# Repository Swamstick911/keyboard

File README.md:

# Mechatron

## About

Mechatron is a 65% mechanical keyboard. It has some features listed below:
- An OLED Display [SSD1306]
- A Rotary Encoder [EC11]
- RGB Underglow
- Tactile Switches

---

## Firmware

The firmware will be KMK which will be written in micropython, as I am using a Raspberry Pi Pico, it makes this easier. Still working on the firmware of the keyboard, for updates check the JOURNAL.md file!

---

## Bill of Materials (BOM)

| Name                                                          | Quantity   | Cost   | Link                                                                                                                                                                                                                                                                                                                                                                                                                                                                                                                                                 |
|:--------------------------------------------------------------|:-----------|:-------|:-----------------------------------------------------------------------------------------------------------------------------------------------------------------------------------------------------------------------------------------------------------------------------------------------------------------------------------------------------------------------------------------------------------------------------------------------------------------------------------------------------------------------------------------------------|
| Gateron EF Grayish                                            | 80         | $18.19 | https://neomacro.in/products/gateron-ef-grayish                                                                                                                                                                                                                                                                                                                                                                                                                                                                                                      |
| Durock Smokey Screw-In Stabilizers V2 (4+1 w/ 6.25u spacebar) | 1          | $18.58 | https://stackskb.com/store/durock-smokey-screw-in-stabilizers-v2/                                                                                                                                                                                                                                                                                                                                                                                                                                                                                    |
| Cherry Profile PBT Keycaps                                    | 1          | $15.15 | https://stackskb.com/store/veekos-gradient-keycaps-cherry-profile-135-keys/                                                                                                                                                                                                                                                                                                                                                                                                                                                                          |
| Diode 1N4148 Through-Hole                                     | 100        | $1.17  | https://www.amazon.in/dp/B084ZP5BJ3?ref_=cm_sw_r_cp_ud_dp_YPW3WFYTE31QA18570D1&_encoding=UTF8&psc=1                                                                                                                                                                                                                                                                                                                                                                                                                                                  |
| WS2812B RGB LED                                               | 8          | $2.76  | https://www.adafruit.com/product/1655                                                                                                                                                                                                                                                                                                                                                                                                                                                                                                                |
| Header 1x4 (I2C OLED)                                         | 1          | $0.10  | https://www.digikey.in/en/products/detail/amphenol-fci/20021121-00010T4LF/10014539                                                                                                                                                                                                                                                                                                                                                                                                                                                                   |
| OLED                                                          | 1          | $1.92  | https://www.amazon.in/Robodo-Electronics-D1286464-Display-Arduino/dp/B07B92SFJV?crid=22PDBSONP7I84&dib=eyJ2IjoiMSJ9._fc6m2CiLg2C4zbCzTKu5yG8fXhyDDnEzcq-tkJ5ONFzDwy16N8zf2l60QPbqxWQhk4mFtEJ5IH2EA0xsyK-mwiNFWFD_w9vg1a7mg-NjWp_56AFy1OO9-iygwyQk9sB69dxvDaZvVmbT36XL2-eg49dpzfKXk0bx13VoBi1Hhb1vG3RQP0P7Z7VCThHe2NjnwkjVfkNtYHWYOWzaG1JvLpacVPaWzxN3Uhdzq5UvlM.GtWvXxquAYLzol9vmMcDAWZhkUVFSIQtM6K3fH87alc&dib_tag=se&keywords=0.91%2Binch%2Boled%2Bdisplay%2Bi2c&qid=1755270026&sprefix=0.91%2Binch%2Boled%2Bdisplay%2Bi2%2Caps%2C384&sr=8-11&th=1 |
| Rotary Encoder EC11 w/ Push                                   | 1          | $2.00  | https://www.adafruit.com/product/377                                                                                                                                                                                                                                                                                                                                                                                                                                                                                                                 |
| I2C Expander (PCF8574)                                        | 1          | $0.83  | https://www.digikey.in/en/products/detail/nxp-usa-inc/PCF8574T-3-518/735505                                                                                                                                                                                                                                                                                                                                                                                                                                                                          |
| M3 x 20mm Bolt                                                | 15         | $1.73  | https://www.amazon.in/dp/B0CX99K2RL?ref_=cm_sw_r_cp_ud_dp_WPFQM677EMXT3KKH904P&_encoding=UTF8                                                                                                                                                                                                                                                                                                                                                                                                                                                        |
| M3 Nuts                                                       | 8          | $1.16  | https://www.amazon.in/dp/B09J92WY5Q?ref_=cm_sw_r_cp_ud_dp_7TEKARN0PX76YMEZR3TW&_encoding=UTF8&psc=1                                                                                                                                                                                                                                                                                                                                                                                                                                                  |
| M3 x 5mm Heatset Insert                                       | 25         | $2.09  | https://www.amazon.in/dp/B0CX1BS7DJ?ref_=cm_sw_r_cp_ud_dp_13RMQGNJ1CXSNS92NXVW                                                                                                                                                                                                                                                                                                                                                                                                                                                                       |
| PCB - (Black Color)                                           | 5          | $69.99 | nan                                                                                                                                                                                                                                                                                                                                                                                                                                                                                                                                                  |
| Raspberry Pi Pico                                             | 1          | $5.19  | https://www.amazon.in/Raspberry-Pi-Headers-Soldered-Micro/dp/B08WPNM7JB/ref=sr_1_2?sr=8-2                                                                                                                                                                                                                                                                                                                                                                                                                                                            |
| Case - top                                                    | mid        | bottom | 1                                                                                                                                                                                                                                                                                                                                                                                                                                                                                                                                                    |
---

## Images:

---

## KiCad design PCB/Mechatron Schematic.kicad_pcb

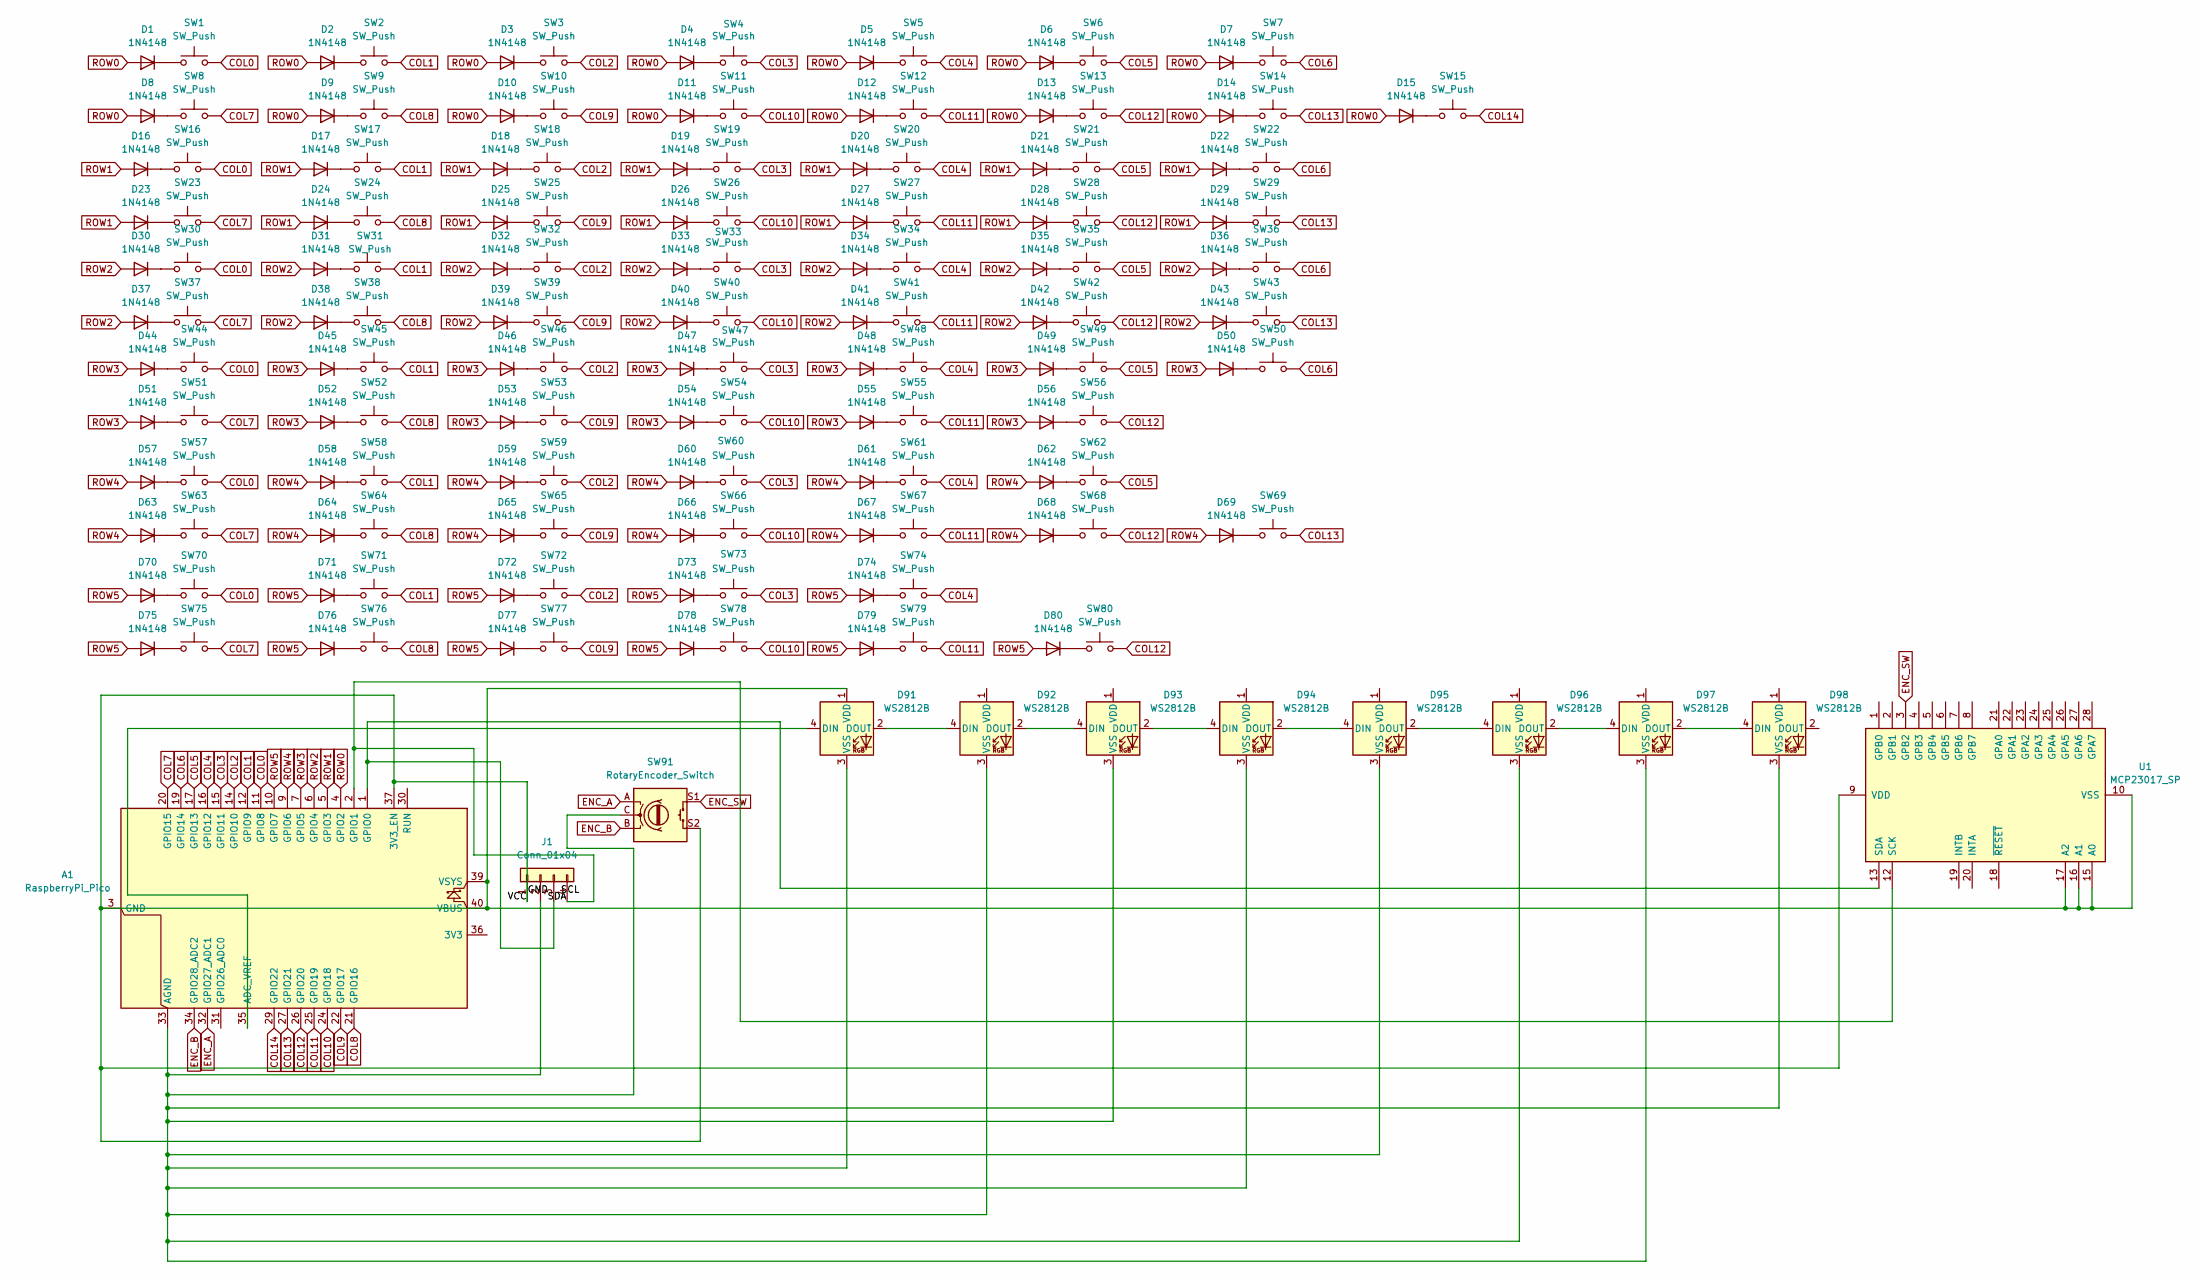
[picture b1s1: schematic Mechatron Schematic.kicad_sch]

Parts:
A1: RaspberryPi_Pico; RaspberryPi_Pico_Common_Unspecified
D1, D2, D3, D4, D5, D6, D7, D8, D9, D10, D11, D12, D13, D14, D15, D16, D17, D18, D19, D20, D21, D22, D23, D24, D25, D26, D27, D28, D29, D30, D31, D32, D33, D34, D35, D36, D37, D38, D39, D40, D41, D42, D43, D44, D45, D46, D47, D48, D49, D50, D51, D52, D53, D54, D55, D56, D57, D58, D59, D60, D61, D62, D63, D64, D65, D66, D67, D68, D69, D70, D71, D72, D73, D74, D75, D76, D77, D78, D79, D80: 1N4148; D_DO-35_SOD27_P7.62mm_Horizontal
D91, D92, D93, D94, D95, D96, D97, D98: WS2812B; LED_WS2812B_PLCC4_5.0x5.0mm_P3.2mm
J1: Conn_01x04; PinHeader_1x04_P2.54mm_Vertical
SW1, SW2, SW3, SW4, SW5, SW6, SW7, SW8, SW9, SW10, SW11, SW12, SW13, SW14, SW15, SW16, SW17, SW18, SW19, SW20, SW21, SW22, SW23, SW24, SW25, SW26, SW27, SW28, SW31, SW32, SW33, SW34, SW35, SW36, SW37, SW38, SW39, SW40, SW41, SW42, SW45, SW46, SW47, SW48, SW49, SW50, SW51, SW52, SW53, SW54, SW55, SW58, SW59, SW60, SW61, SW62, SW63, SW64, SW65, SW66, SW67, SW69, SW78, SW79, SW80: SW_Push; SW_Cherry_MX_1.00u_PCB
SW29: SW_Push; SW_Cherry_MX_2.00u_PCB
SW30, SW43: SW_Push; SW_Cherry_MX_1.50u_PCB
SW44: SW_Push; SW_Cherry_MX_1.75u_PCB
SW56, SW57: SW_Push; SW_Cherry_MX_2.25u_PCB
SW68: SW_Push; SW_Cherry_MX_2.75u_PCB
SW70, SW71, SW72, SW74, SW75, SW76, SW77: SW_Push; SW_Cherry_MX_1.25u_PCB
SW73: SW_Push; SW_Cherry_MX_6.25u_PCB
SW91: RotaryEncoder_Switch; RotaryEncoder_Alps_EC11E-Switch_Vertical_H20mm
U1: MCP23017_SP; DIP-28_W7.62mm

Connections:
/GND: A1.3 (GND), A1.8 (GND), A1.13 (GND), A1.18 (GND), A1.23 (GND), A1.28 (GND), A1.37 (3V3_EN), A1.38 (GND), A1.39 (VSYS), A1.40 (VBUS), D91.1 (VDD), J1.1, SW91.S2, U1.9 (VDD), U1.10 (VSS), U1.15 (A0), U1.16 (A1), U1.17 (A2)
COL0: A1.11 (GPIO8), SW1.2, SW16.2, SW30.2, SW44.2, SW57.2, SW70.2
COL1: A1.12 (GPIO9), SW2.2, SW17.2, SW31.2, SW45.2, SW58.2, SW71.2
COL2: A1.14 (GPIO10), SW3.2, SW18.2, SW32.2, SW46.2, SW59.2, SW72.2
COL3: A1.15 (GPIO11), SW4.2, SW19.2, SW33.2, SW47.2, SW60.2, SW73.2
COL4: A1.16 (GPIO12), SW5.2, SW20.2, SW34.2, SW48.2, SW61.2, SW74.2
COL5: A1.17 (GPIO13), SW6.2, SW21.2, SW35.2, SW49.2, SW62.2
COL6: A1.19 (GPIO14), SW7.2, SW22.2, SW36.2, SW50.2
COL7: A1.20 (GPIO15), SW8.2, SW23.2, SW37.2, SW51.2, SW63.2, SW75.2
COL8: A1.21 (GPIO16), SW9.2, SW24.2, SW38.2, SW52.2, SW64.2, SW76.2
COL9: A1.22 (GPIO17), SW10.2, SW25.2, SW39.2, SW53.2, SW65.2, SW77.2
COL10: A1.24 (GPIO18), SW11.2, SW26.2, SW40.2, SW54.2, SW66.2, SW78.2
COL11: A1.25 (GPIO19), SW12.2, SW27.2, SW41.2, SW55.2, SW67.2, SW79.2
COL12: A1.26 (GPIO20), SW13.2, SW28.2, SW42.2, SW56.2, SW68.2, SW80.2
COL13: A1.27 (GPIO21), SW14.2, SW29.2, SW43.2, SW69.2
COL14: A1.29 (GPIO22), SW15.2
ENC_A: A1.32 (GPIO27_ADC1), SW91.A
ENC_B: A1.34 (GPIO28_ADC2), SW91.B
ENC_SW: SW91.S1, U1.3 (GPB2)
unnamed: A1.35 (ADC_VREF), D91.4 (DIN)
unnamed: A1.33 (AGND), D91.3 (VSS), D92.3 (VSS), D93.3 (VSS), D94.3 (VSS), D95.3 (VSS), D96.3 (VSS), D97.3 (VSS), D98.3 (VSS), J1.2, SW91.C
unnamed: A1.1 (GPIO0), J1.3, U1.13 (SDA)
unnamed: A1.2 (GPIO1), J1.4, U1.12 (SCK)
unnamed: D1.1 (K), SW1.1
unnamed: D2.1 (K), SW2.1
unnamed: D3.1 (K), SW3.1
unnamed: D4.1 (K), SW4.1
unnamed: D5.1 (K), SW5.1
unnamed: D6.1 (K), SW6.1
unnamed: D7.1 (K), SW7.1
unnamed: D8.1 (K), SW8.1
unnamed: D9.1 (K), SW9.1
unnamed: D10.1 (K), SW10.1
unnamed: D11.1 (K), SW11.1
unnamed: D12.1 (K), SW12.1
unnamed: D13.1 (K), SW13.1
unnamed: D14.1 (K), SW14.1
unnamed: D15.1 (K), SW15.1
unnamed: D16.1 (K), SW16.1
unnamed: D17.1 (K), SW17.1
unnamed: D18.1 (K), SW18.1
unnamed: D19.1 (K), SW19.1
unnamed: D20.1 (K), SW20.1
unnamed: D21.1 (K), SW21.1
unnamed: D22.1 (K), SW22.1
unnamed: D23.1 (K), SW23.1
unnamed: D24.1 (K), SW24.1
unnamed: D25.1 (K), SW25.1
unnamed: D26.1 (K), SW26.1
unnamed: D27.1 (K), SW27.1
unnamed: D28.1 (K), SW28.1
unnamed: D29.1 (K), SW29.1
unnamed: D30.1 (K), SW30.1
unnamed: D31.1 (K), SW31.1
unnamed: D32.1 (K), SW32.1
unnamed: D33.1 (K), SW33.1
unnamed: D34.1 (K), SW34.1
unnamed: D35.1 (K), SW35.1
unnamed: D36.1 (K), SW36.1
unnamed: D37.1 (K), SW37.1
unnamed: D38.1 (K), SW38.1
unnamed: D39.1 (K), SW39.1
unnamed: D40.1 (K), SW40.1
unnamed: D41.1 (K), SW41.1
unnamed: D42.1 (K), SW42.1
unnamed: D43.1 (K), SW43.1
unnamed: D44.1 (K), SW44.1
unnamed: D45.1 (K), SW45.1
unnamed: D46.1 (K), SW46.1
unnamed: D47.1 (K), SW47.1
unnamed: D48.1 (K), SW48.1
unnamed: D49.1 (K), SW49.1
unnamed: D50.1 (K), SW50.1
unnamed: D51.1 (K), SW51.1
unnamed: D52.1 (K), SW52.1
unnamed: D53.1 (K), SW53.1
unnamed: D54.1 (K), SW54.1
unnamed: D55.1 (K), SW55.1
unnamed: D56.1 (K), SW56.1
unnamed: D57.1 (K), SW57.1
unnamed: D58.1 (K), SW58.1
unnamed: D59.1 (K), SW59.1
unnamed: D60.1 (K), SW60.1
unnamed: D61.1 (K), SW61.1
unnamed: D62.1 (K), SW62.1
unnamed: D63.1 (K), SW63.1
unnamed: D64.1 (K), SW64.1
unnamed: D65.1 (K), SW65.1
unnamed: D66.1 (K), SW66.1
unnamed: D67.1 (K), SW67.1
unnamed: D68.1 (K), SW68.1
unnamed: D69.1 (K), SW69.1
unnamed: D70.1 (K), SW70.1
unnamed: D71.1 (K), SW71.1
unnamed: D72.1 (K), SW72.1
unnamed: D73.1 (K), SW73.1
unnamed: D74.1 (K), SW74.1
unnamed: D75.1 (K), SW75.1
unnamed: D76.1 (K), SW76.1
unnamed: D77.1 (K), SW77.1
unnamed: D78.1 (K), SW78.1
unnamed: D79.1 (K), SW79.1
unnamed: D80.1 (K), SW80.1
unnamed: D91.2 (DOUT), D92.4 (DIN)
unnamed: D92.2 (DOUT), D93.4 (DIN)
unnamed: D93.2 (DOUT), D94.4 (DIN)
unnamed: D94.2 (DOUT), D95.4 (DIN)
unnamed: D95.2 (DOUT), D96.4 (DIN)
unnamed: D96.2 (DOUT), D97.4 (DIN)
unnamed: D97.2 (DOUT), D98.4 (DIN)
ROW0: A1.4 (GPIO2), D1.2 (A), D2.2 (A), D3.2 (A), D4.2 (A), D5.2 (A), D6.2 (A), D7.2 (A), D8.2 (A), D9.2 (A), D10.2 (A), D11.2 (A), D12.2 (A), D13.2 (A), D14.2 (A), D15.2 (A)
ROW1: A1.5 (GPIO3), D16.2 (A), D17.2 (A), D18.2 (A), D19.2 (A), D20.2 (A), D21.2 (A), D22.2 (A), D23.2 (A), D24.2 (A), D25.2 (A), D26.2 (A), D27.2 (A), D28.2 (A), D29.2 (A)
ROW2: A1.6 (GPIO4), D30.2 (A), D31.2 (A), D32.2 (A), D33.2 (A), D34.2 (A), D35.2 (A), D36.2 (A), D37.2 (A), D38.2 (A), D39.2 (A), D40.2 (A), D41.2 (A), D42.2 (A), D43.2 (A)
ROW3: A1.7 (GPIO5), D44.2 (A), D45.2 (A), D46.2 (A), D47.2 (A), D48.2 (A), D49.2 (A), D50.2 (A), D51.2 (A), D52.2 (A), D53.2 (A), D54.2 (A), D55.2 (A), D56.2 (A)
ROW4: A1.9 (GPIO6), D57.2 (A), D58.2 (A), D59.2 (A), D60.2 (A), D61.2 (A), D62.2 (A), D63.2 (A), D64.2 (A), D65.2 (A), D66.2 (A), D67.2 (A), D68.2 (A), D69.2 (A)
ROW5: A1.10 (GPIO7), D70.2 (A), D71.2 (A), D72.2 (A), D73.2 (A), D74.2 (A), D75.2 (A), D76.2 (A), D77.2 (A), D78.2 (A), D79.2 (A), D80.2 (A)

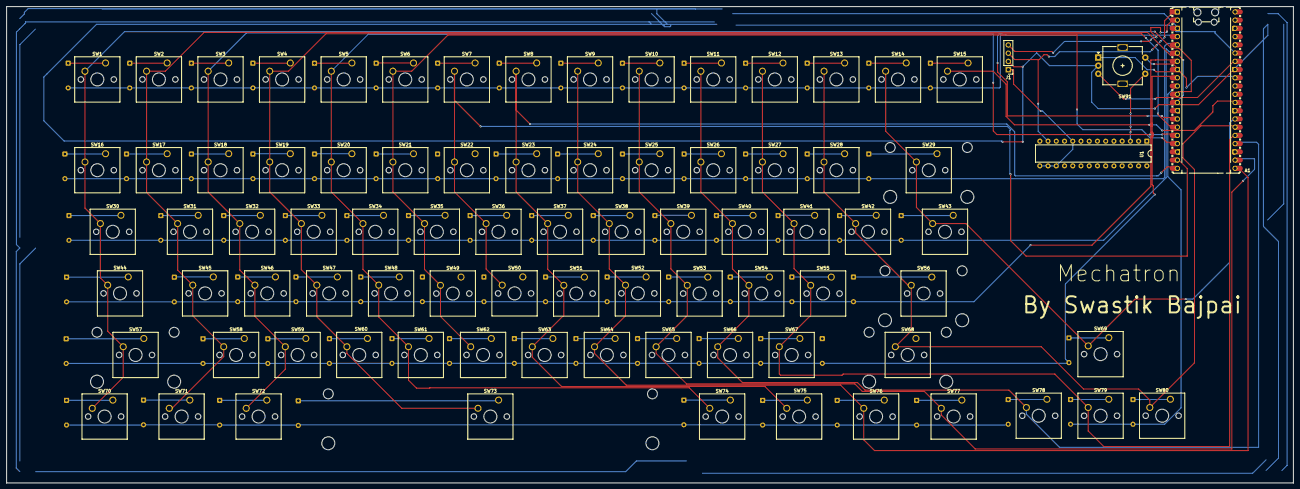
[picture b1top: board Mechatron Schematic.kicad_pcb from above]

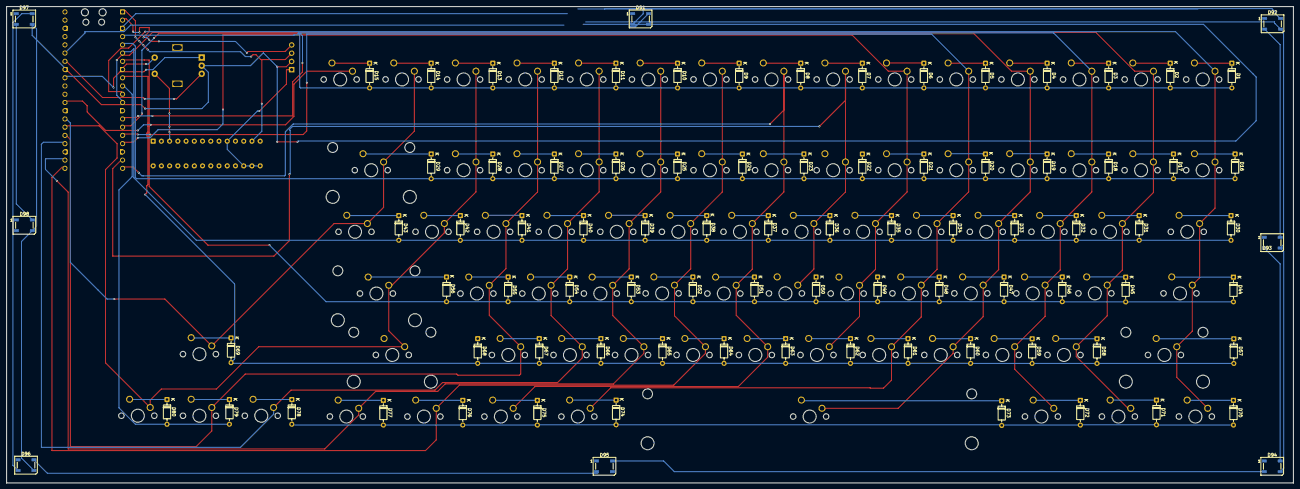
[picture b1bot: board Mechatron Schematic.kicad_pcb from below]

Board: 2 copper layers, 397.0 x 147.0 mm, 172 parts (88 on the bottom side), 116 nets.

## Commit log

2025-06-19 Adding the completed schematic
2025-06-29 Deleting old schematic file
2025-06-29 Adding the new schematic file
2025-06-29 Adding Gerber files
2025-07-23 Adding the CAD files
2025-07-23 Adding the BOM file
2025-07-24 Adding the firmware files
2025-08-02 Removing old CAD files
2025-08-02 Reorganising
2025-08-04 Adding PCB files
2025-08-04 Adding Images to README.md
2025-08-04 Adding BOM to README.md
2025-08-04 Adding the files which were left
2025-08-04 Deleting schematic pdf
2025-08-04 Rename Mechatron Schematic.zip to Gerber.zip
2025-08-15 Deleting old CAD case top file
2025-08-15 Adding new case top file
2025-09-27 Adding the changed PCB file
2025-09-27 Adding the new gerber file
2025-09-27 Deleting old gerber file
